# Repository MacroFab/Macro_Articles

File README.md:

***
###Macro_Articles
***
**Files for MacroFab, INC. engineering blog articles.**

This repository contains files and information for articles written on the MacroFab, INC. engineering blog. 

More information can be found on the [MacroFab, INC. engineering blog](https://macrofab.com/blog/engineering). 

***
**License Information**

This project is under the [Creative Commons Attribution-ShareAlike 4.0 International License](LICENSE.md). These files are provided with no warranty and should be used at your own risk. 

***
**Directory listing of the repository**

| Directory | Description |
|---|---|
| AlteraUSBBlaster2TC | Connects the Altera USB Blaster to a TC2050 Tag-Connect Cable. |
| AVR_Tag-Connect | AVR ATmega328P-AU example board using Tag-Connect for programming. |
| AVRISP2TC | Connects AVR ISP programmers to a TC2030 Tag-Connect Cable. | 
| EFM8_Tag-Connect | Tiny example board using Tag-Connect for the EGM8 MCU series. |
| Macro_Duino | MacroFab's version of the ever popular Arduino. Useful for electronic prototyping. |
| MEP_EP_122 | Particle.io Podcast Episode. This is the software written for that episode. |
| MEP_SAO_DC26 | Shitty AddOn for DefCon 26 |
| PCM5122_DAC | DAC PCB board and Test Fixture Files. |
| Resistor_Resistor | 40000 Resistor Array. Designed for the MEP prodcast. |
| SiLabs2TC | Connects the Silicon Labs USB Debug Adapter to a TC2030 Tag-Connect Cable. |
| Simple Programming Fixture | How to design a [simple pogo pin programming fixture](https://macrofab.com/blog/design-build-simple-programming-fixture/). |
| SWD2TC | Connects STLink V2 to a TC2030 Tag-Connect Cable. |
| USB_Type-C_Test | A Parallax Propeller based board that connects over a USB Type-C connector. |

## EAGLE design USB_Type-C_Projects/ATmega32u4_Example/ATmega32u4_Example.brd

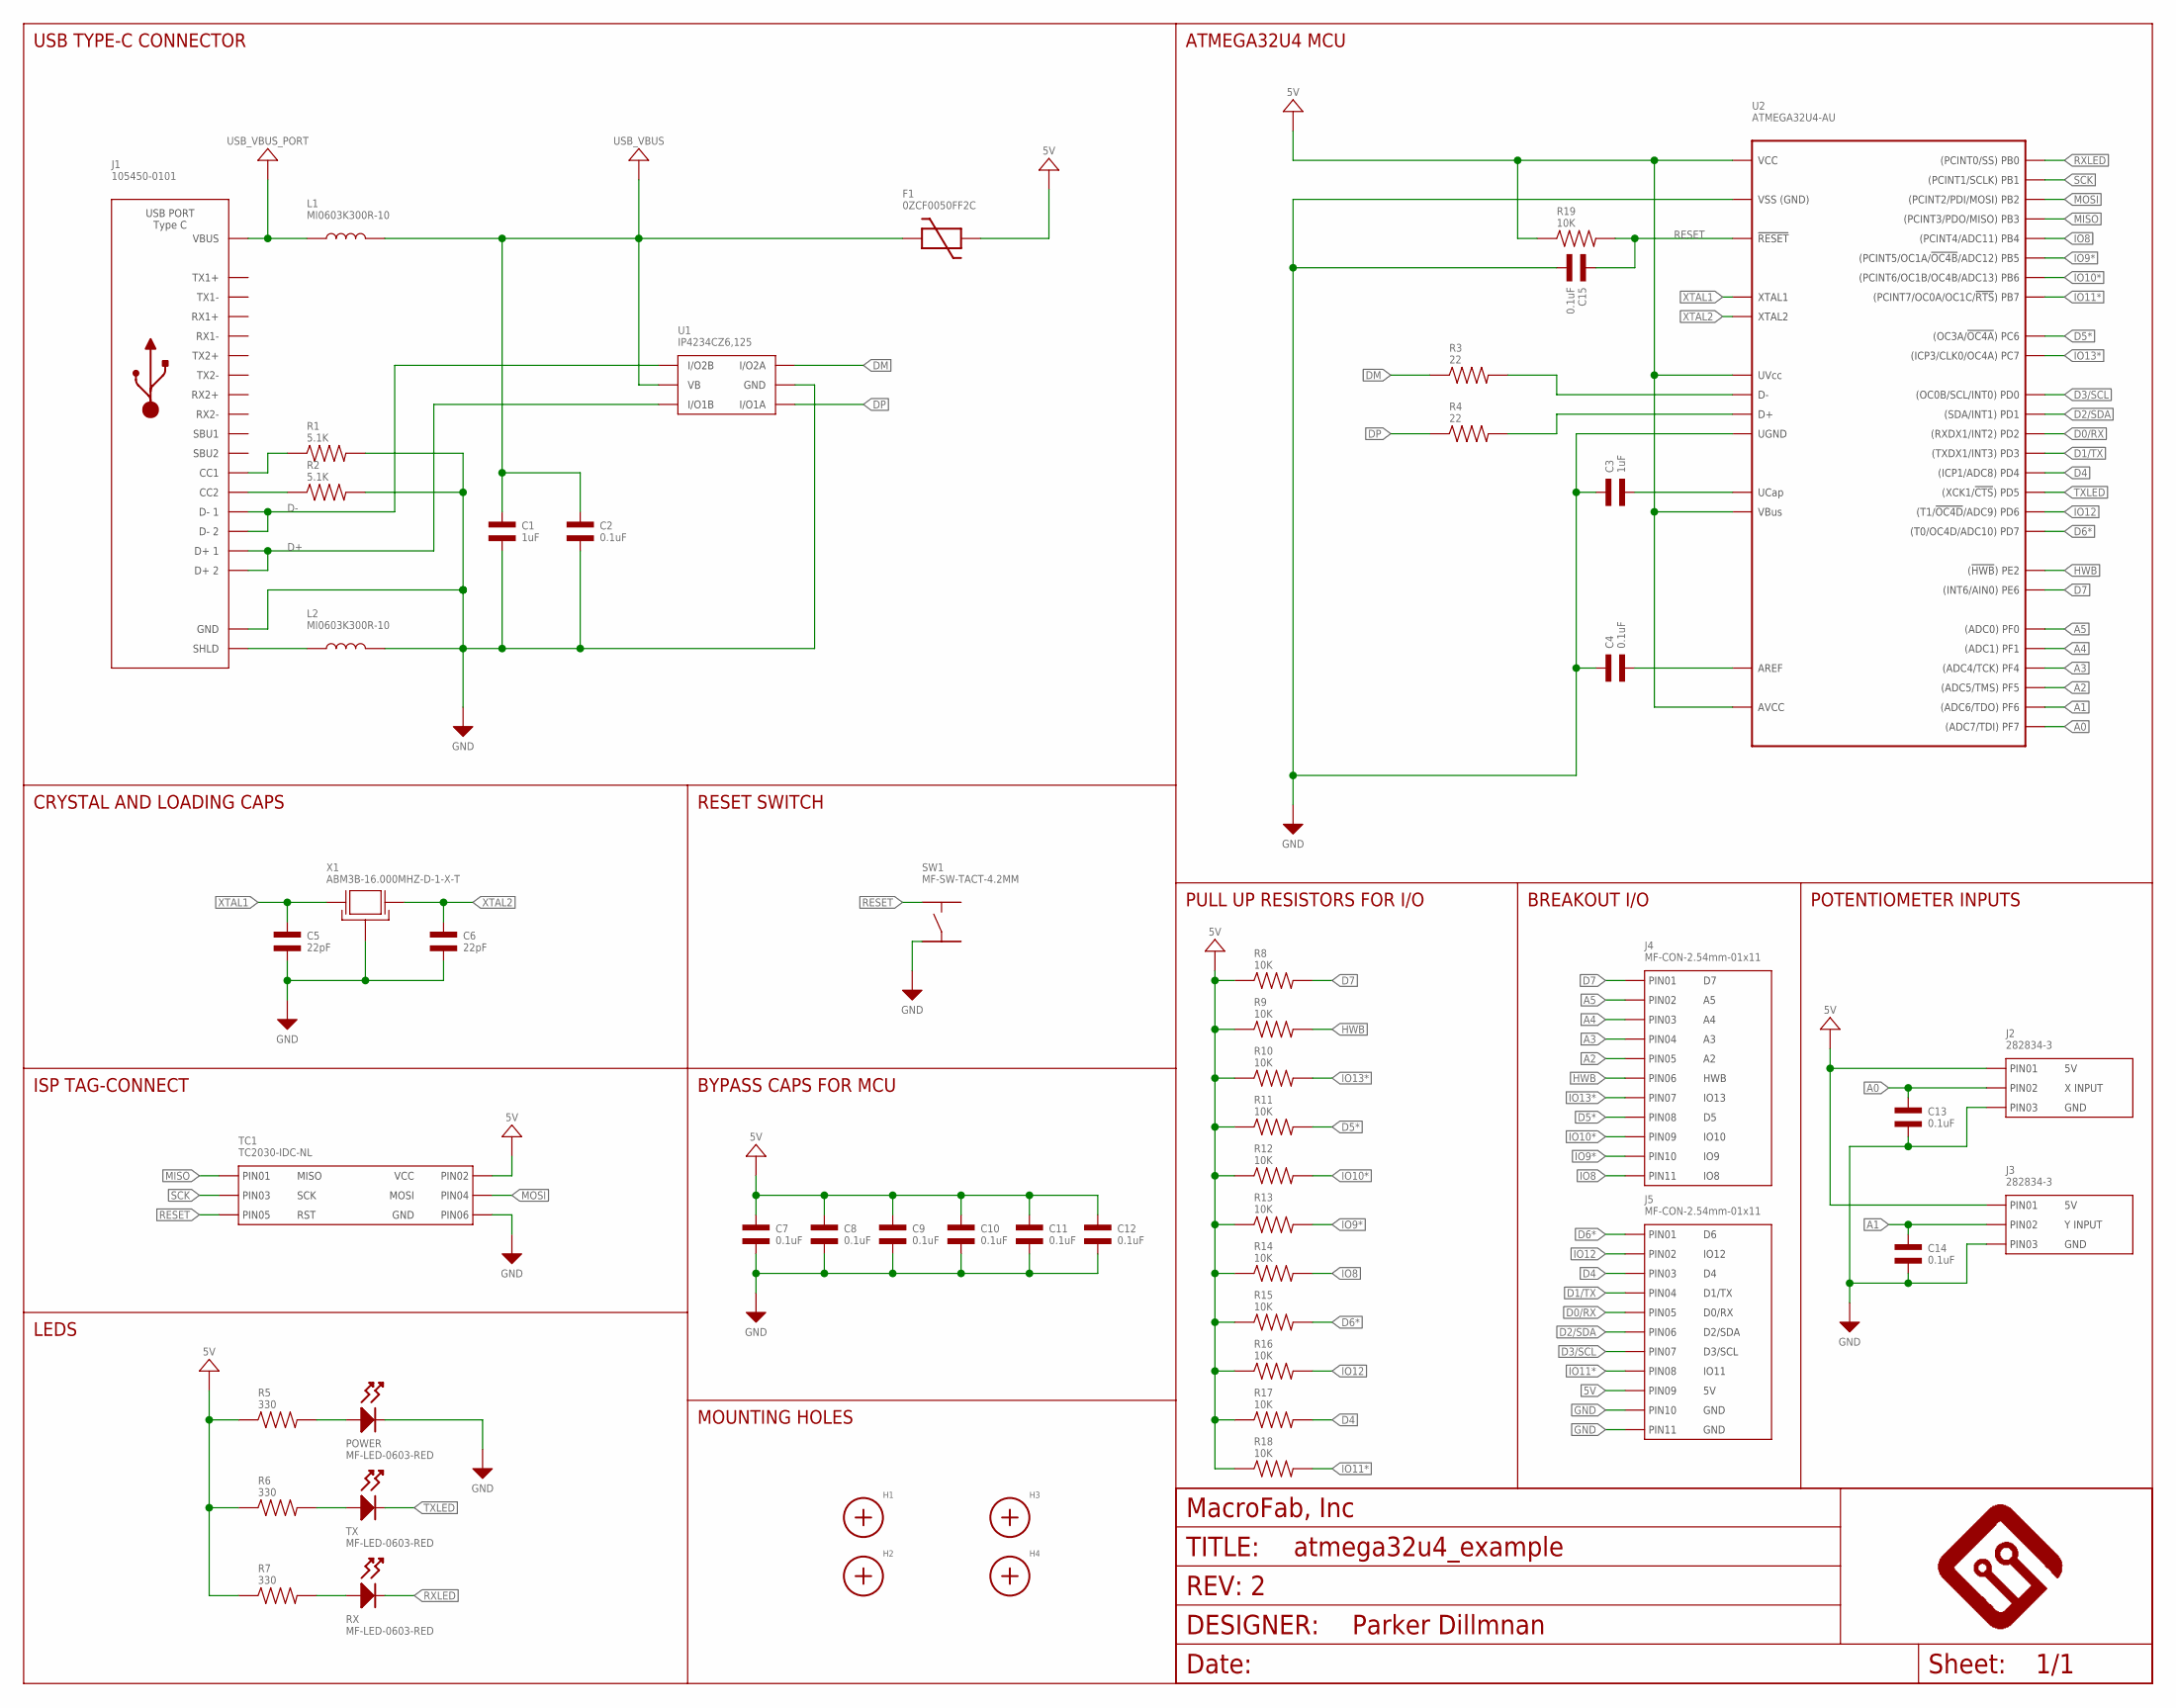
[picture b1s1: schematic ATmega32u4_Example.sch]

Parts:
C1, C3: 1uF; C0603; MPN MF-CAP-0603-1uF
C2, C4, C7, C8, C9, C10, C11, C12, C13, C14, C15: 0.1uF; C0603; MPN MF-CAP-0603-0.1uF
C5, C6: 22pF; C0603; MPN MF-CAP-0603-22pF
F1: 0ZCF0050FF2C; 2920; MPN 0ZCF0050FF2C
FRAME1: MF_FRAMEDEFAULT; MF_FRAME_DEFAULT
H1, H2, H3, H4: MOUNT_HOLE150MIL; MOUNT_HOLE_150MIL
J1: 105450-0101; MPN 105450-0101
J2, J3: 282834-3
J4, J5: MF-CON-2.54mm-01x11; PTH_2.54MM_01X11
L1, L2: MI0603K300R-10; L0603; MPN MI0603K300R-10
POWER: MF-LED-0603-RED; LED0603
R1, R2: 5.1K; R0603; MPN ERJ-3EKF5101V
R3, R4: 22; R0603; MPN MF-RES-0603-22
R5, R6, R7: 330; R0603; MPN MF-RES-0603-330
R8, R9, R10, R11, R12, R13, R14, R15, R16, R17, R18, R19: 10K; R0603; MPN MF-RES-0603-10K
RX: MF-LED-0603-RED; LED0603
SW1: MF-SW-TACT-4.2MM; TACT4.2MM
TC1: TC2030-IDC-NL
TX: MF-LED-0603-RED; LED0603
U1: IP4234CZ6,125; IP4234CZ6_SOT-457-6; MPN IP4234CZ6,125
U2: ATMEGA32U4-AU; TQFP44
X1: ABM3B-16.000MHZ-D-1-X-T; 5MMX3.2MM; MPN ABM3B-16.000MHZ-D-1-X-T

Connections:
5V: C7.P$1, C8.P$1, C9.P$1, C10.P$1, C11.P$1, C12.P$1, F1.2, J2.P$1 (PIN1), J3.P$1 (PIN1), J5.P$9 (PIN9), R5.P$1, R6.P$1, R7.P$1, R8.P$1, R9.P$1, R10.P$1, R11.P$1, R12.P$1, R13.P$1, R14.P$1, R15.P$1, R16.P$1, R17.P$1, R18.P$1, R19.P$1, TC1.P$2 (PIN2), U2.P$2 (UVCC), U2.P$7 (VBUS), U2.P$14 (VCC), U2.P$24 (AVCC), U2.P$34 (VCC), U2.P$44 (AVCC)
A0: C13.P$1, J2.P$2 (PIN2), U2.P$36 (PF7)
A1: C14.P$1, J3.P$2 (PIN2), U2.P$37 (PF6)
A2: J4.P$5 (PIN5), U2.P$38 (PF5)
A3: J4.P$4 (PIN4), U2.P$39 (PF4)
A4: J4.P$3 (PIN3), U2.P$40 (PF1)
A5: J4.P$2 (PIN2), U2.P$41 (PF0)
CC1: J1.A5 (CC1), R1.P$1
CC2: J1.B5 (CC2), R2.P$1
D0/RX: J5.P$5 (PIN5), U2.P$20 (PD2)
D1/TX: J5.P$4 (PIN4), U2.P$21 (PD3)
D2/SDA: J5.P$6 (PIN6), U2.P$19 (PD1)
D3/SCL: J5.P$7 (PIN7), U2.P$18 (PD0)
D4: J5.P$3 (PIN3), R17.P$2, U2.P$25 (PD4)
D5*: J4.P$8 (PIN8), R11.P$2, U2.P$31 (PC6)
D6*: J5.P$1 (PIN1), R15.P$2, U2.P$27 (PD7)
D7: J4.P$1 (PIN1), R8.P$2, U2.P$1 (PE6)
D+: J1.A6 (D+1), J1.B6 (D+2), U1.3 (I/O1B)
D-: J1.A7 (D-1), J1.B7 (D-2), U1.4 (I/O2B)
DM: R3.P$1, U1.6 (I/O2A)
DP: R4.P$1, U1.1 (I/O1A)
GND: C1.P$2, C2.P$2, C3.P$1, C4.P$1, C5.P$2, C6.P$2, C7.P$2, C8.P$2, C9.P$2, C10.P$2, C11.P$2, C12.P$2, C13.P$2, C14.P$2, C15.P$2, J1.A1 (GND), J1.A12 (GND), J1.B1 (GND), J1.B12 (GND), J2.P$3 (PIN3), J3.P$3 (PIN3), J5.P$10 (PIN10), J5.P$11 (PIN11), L2.P$2, POWER.CATHODE, R1.P$2, R2.P$2, SW1.P$3, TC1.P$6 (PIN6), U1.2 (GND), U2.P$5 (UGND), U2.P$15 (GND), U2.P$23 (GND), U2.P$35 (GND), U2.P$43 (GND), X1.P$2 (GND), X1.P$4 (GND)
HWB: J4.P$6 (PIN6), R9.P$2, U2.P$33 (PE2)
IO8: J4.P$11 (PIN11), R14.P$2, U2.P$28 (PB4)
IO9*: J4.P$10 (PIN10), R13.P$2, U2.P$29 (PB5)
IO10*: J4.P$9 (PIN9), R12.P$2, U2.P$30 (PB6)
IO11*: J5.P$8 (PIN8), R18.P$2, U2.P$12 (PB7)
IO12: J5.P$2 (PIN2), R16.P$2, U2.P$26 (PD6)
IO13*: J4.P$7 (PIN7), R10.P$2, U2.P$32 (PC7)
MISO: TC1.P$1 (PIN1), U2.P$11 (PB3)
MOSI: TC1.P$4 (PIN4), U2.P$10 (PB2)
unnamed: R3.P$2, U2.P$3 (D-)
unnamed: R4.P$2, U2.P$4 (D+)
unnamed: C3.P$2, U2.P$6 (UCAP)
unnamed: C4.P$2, U2.P$42 (AREF)
unnamed: POWER.ANODE, R5.P$2
unnamed: R6.P$2, TX.ANODE
unnamed: R7.P$2, RX.ANODE
RESET: C15.P$1, R19.P$2, SW1.P$1, TC1.P$5 (PIN5), U2.P$13 (!RESET)
RXLED: RX.CATHODE, U2.P$8 (PB0)
SCK: TC1.P$3 (PIN3), U2.P$9 (PB1)
SHEILD1: J1.S_T1 (SHLD), J1.S_T2 (SHLD), J1.S_T3 (SHLD), J1.S_T4 (SHLD), L2.P$1
TXLED: TX.CATHODE, U2.P$22 (PD5)
USB_VBUS: C1.P$1, C2.P$1, F1.1, L1.P$2, U1.5 (VB)
USB_VBUS_PORT: J1.A4 (VBUS), J1.A9 (VBUS), J1.B4 (VBUS), J1.B9 (VBUS), L1.P$1
XTAL1: C5.P$1, U2.P$17 (XTAL1), X1.P$1 (X0)
XTAL2: C6.P$1, U2.P$16 (XTAL2), X1.P$3 (X1)

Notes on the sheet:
LEDS
ISP TAG-CONNECT
CRYSTAL AND LOADING CAPS
RESET SWITCH
USB TYPE-C CONNECTOR
BYPASS CAPS FOR MCU
MOUNTING HOLES
ATMEGA32U4 MCU
PULL UP RESISTORS FOR I/O
BREAKOUT I/O
POTENTIOMETER INPUTS

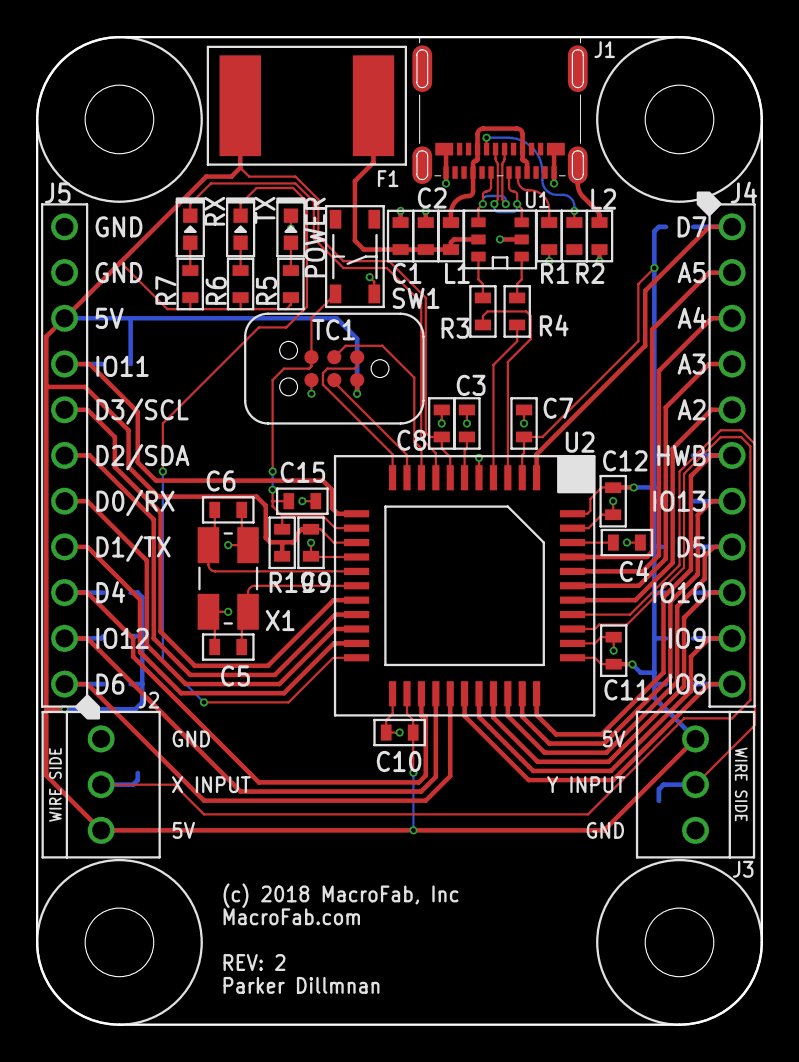
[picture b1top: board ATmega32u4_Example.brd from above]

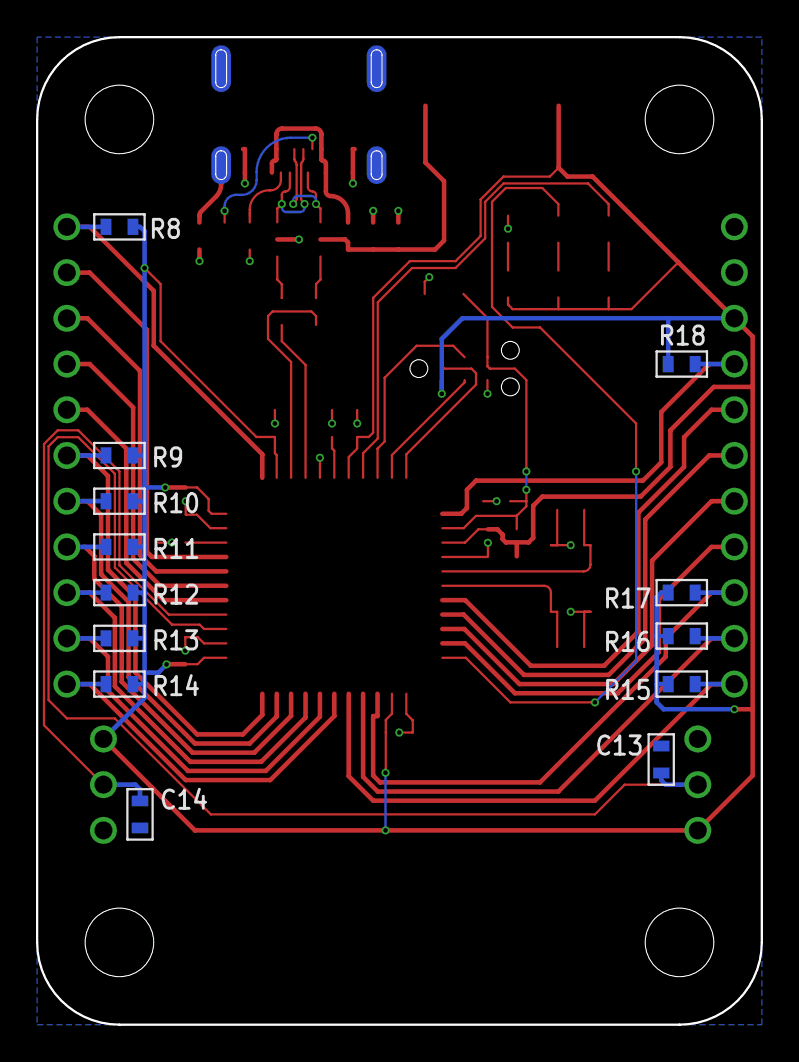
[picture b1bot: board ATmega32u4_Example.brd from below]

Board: 2 copper layers, 40.3 x 54.9 mm, 55 parts (13 on the bottom side), 47 nets.

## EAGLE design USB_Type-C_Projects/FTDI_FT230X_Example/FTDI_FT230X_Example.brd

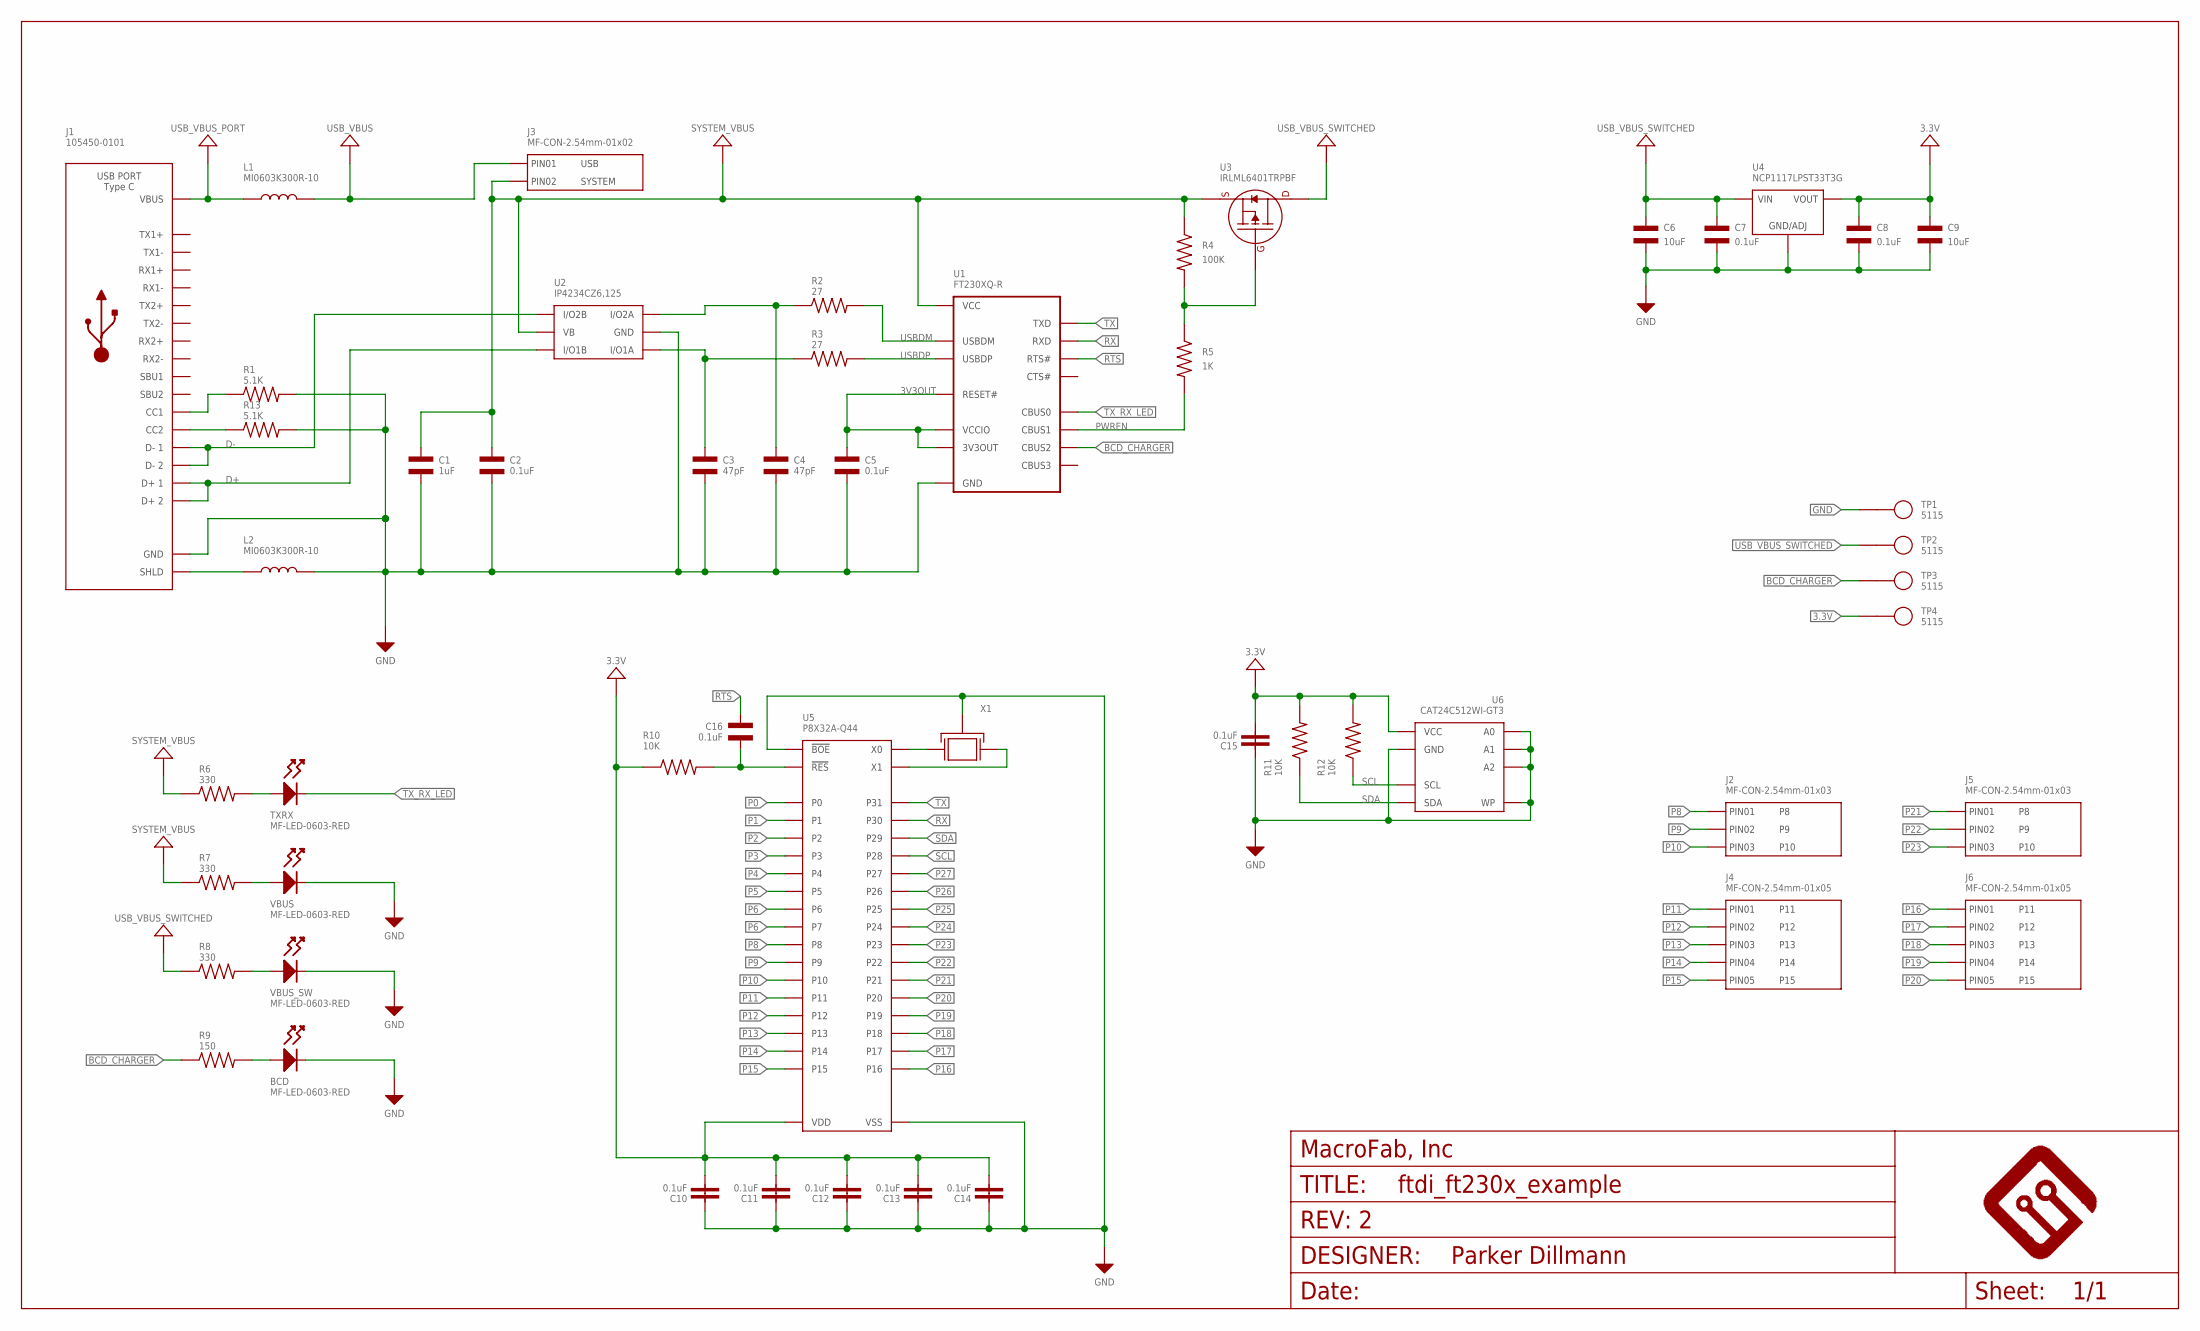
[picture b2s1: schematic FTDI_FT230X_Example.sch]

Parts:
BCD: MF-LED-0603-RED; LED0603
C1: 1uF; C0603; MPN MF-CAP-0603-1uF
C2, C5, C7, C8, C16: 0.1uF; C0603; MPN MF-CAP-0603-0.1uF
C3, C4: 47pF; C0603; MPN C0603C470J1GACTU
C6, C9: 10uF; C1206; MPN MF-CAP-1206-10uF
C10, C11, C12, C13, C14, C15: 0.1uF; 0603; MPN MF-CAP-0603-0.1uF
FRAME1: MF_FRAMEDEFAULT; MF_FRAME_DEFAULT
J1: 105450-0101; MPN 105450-0101
J2, J5: MF-CON-2.54mm-01x03; PTH_2.54MM_01X03
J3: MF-CON-2.54mm-01x02; PTH_2.54MM_01X02
J4, J6: MF-CON-2.54mm-01x05; PTH_2.54MM_01X05
L1, L2: MI0603K300R-10; L0603; MPN MI0603K300R-10
R1, R13: 5.1K; R0603; MPN ERJ-3EKF5101V
R2, R3: 27; R0603; MPN MF-RES-0603-27
R4: 100K; R0603; MPN MF-RES-0603-100K
R5: 1K; R0603; MPN MF-RES-0603-1K
R6, R7, R8: 330; R0603; MPN MF-RES-0603-330
R9: 150; R0603; MPN ERJ-3EKF1500V
R10, R11, R12: 10K; 0603; MPN MF-RES-0603-10K
TP1, TP2, TP3, TP4: 5115; KEYSTONE_5115-5119; MPN Keystone 5115
TXRX: MF-LED-0603-RED; LED0603
U1: FT230XQ-R; FT230X_QFN-16; MPN FT230XQ-R
U2: IP4234CZ6,125; IP4234CZ6_SOT-457-6; MPN IP4234CZ6,125
U3: IRLML6401TRPBF; SOT-23-3; MPN IRLML6401TRPBF
U4: NCP1117LPST33T3G; SOT-223-3
U5: P8X32A-Q44; P8X32A_LQFP-44; MPN P8X32A-Q44
U6: CAT24C512WI-GT3; SOIC-8_W; MPN CAT24C512WI-GT3
VBUS: MF-LED-0603-RED; LED0603
VBUS_SW: MF-LED-0603-RED; LED0603
X1: ABMM-6.000MHZ-B2-T; 7MMX5MM; MPN ABMM-6.000MHZ-B2-T

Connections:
3.3V: C8.P$1, C9.P$1, C10.2, C11.2, C12.2, C13.2, C14.2, C15.2, R10.1, R11.2, R12.2, TP4.P$1, U4.P$1 (VOUT), U4.P$3 (VOUT), U5.8 (VDD), U5.18 (VDD), U5.30 (VDD), U5.40 (VDD), U6.8 (VCC)
3V3OUT: C5.P$1, U1.1 (VCCIO), U1.8 (3V3OUT), U1.9 (RESET#)
BCD_CHARGER: R9.P$1, TP3.P$1, U1.5 (CBUS2)
CC1: J1.A5 (CC1), R1.P$1
CC2: J1.B5 (CC2), R13.P$1
D+: J1.A6 (D+1), J1.B6 (D+2), U2.3 (I/O1B)
D-: J1.A7 (D-1), J1.B7 (D-2), U2.4 (I/O2B)
GND: BCD.CATHODE, C1.P$2, C2.P$2, C3.P$2, C4.P$2, C5.P$2, C6.P$2, C7.P$2, C8.P$2, C9.P$2, C10.1, C11.1, C12.1, C13.1, C14.1, C15.1, J1.A1 (GND), J1.A12 (GND), J1.B1 (GND), J1.B12 (GND), L2.P$2, R1.P$2, R13.P$2, TP1.P$1, U1.3 (GND), U1.13 (GND), U1.PAD (GND), U2.2 (GND), U4.P$2 (GND/ADJ), U5.5 (VSS), U5.6 (!BOE), U5.17 (VSS), U5.27 (VSS), U5.39 (VSS), U6.1 (A0), U6.2 (A1), U6.3 (A2), U6.4 (GND), U6.7 (WP), VBUS.CATHODE, VBUS_SW.CATHODE, X1.P$2 (GND), X1.P$4 (GND)
unnamed: R4.P$2, R5.P$1, U3.1 (GATE)
unnamed: J1.S_T1 (SHLD), J1.S_T2 (SHLD), J1.S_T3 (SHLD), J1.S_T4 (SHLD), L2.P$1
unnamed: R6.P$2, TXRX.ANODE
unnamed: R7.P$2, VBUS.ANODE
unnamed: R8.P$2, VBUS_SW.ANODE
unnamed: BCD.ANODE, R9.P$2
unnamed: C3.P$1, R3.P$1, U2.1 (I/O1A)
unnamed: C4.P$1, R2.P$1, U2.6 (I/O2A)
P0: U5.41 (P0)
P1: U5.42 (P1)
P2: U5.43 (P2)
P3: U5.44 (P3)
P4: U5.1 (P4)
P5: U5.2 (P5)
P6: U5.3 (P6)
P7: U5.4 (P7)
P8: J2.P$1 (PIN1), U5.9 (P8)
P9: J2.P$2 (PIN2), U5.10 (P9)
P10: J2.P$3 (PIN3), U5.11 (P10)
P11: J4.P$1 (PIN1), U5.12 (P11)
P12: J4.P$2 (PIN2), U5.13 (P12)
P13: J4.P$3 (PIN3), U5.14 (P13)
P14: J4.P$4 (PIN4), U5.15 (P14)
P15: J4.P$5 (PIN5), U5.16 (P15)
P16: J6.P$1 (PIN1), U5.19 (P16)
P17: J6.P$2 (PIN2), U5.20 (P17)
P18: J6.P$3 (PIN3), U5.21 (P18)
P19: J6.P$4 (PIN4), U5.22 (P19)
P20: J6.P$5 (PIN5), U5.23 (P20)
P21: J5.P$1 (PIN1), U5.24 (P21)
P22: J5.P$2 (PIN2), U5.25 (P22)
P23: J5.P$3 (PIN3), U5.26 (P23)
P24: U5.31 (P24)
P25: U5.32 (P25)
P26: U5.33 (P26)
P27: U5.34 (P27)
PWREN: R5.P$2, U1.11 (CBUS1)
RES: C16.P$2, R10.2, U5.7 (!RES)
RTS: C16.P$1, U1.16 (RTS#)
RX: U1.2 (RXD), U5.37 (P30)
SCL: R12.1, U5.35 (P28), U6.6 (SCL)
SDA: R11.1, U5.36 (P29), U6.5 (SDA)
SYSTEM_VBUS: C1.P$1, C2.P$1, J3.P$2 (PIN2), R4.P$1, R6.P$1, R7.P$1, U1.10 (VCC), U2.5 (VB), U3.2 (SOURCE)
TX: U1.15 (TXD), U5.38 (P31)
TX_RX_LED: TXRX.CATHODE, U1.12 (CBUS0)
USBDM: R2.P$2, U1.7 (USBDM)
USBDP: R3.P$2, U1.6 (USBDP)
USB_VBUS: J3.P$1 (PIN1), L1.P$2
USB_VBUS_PORT: J1.A4 (VBUS), J1.A9 (VBUS), J1.B4 (VBUS), J1.B9 (VBUS), L1.P$1
USB_VBUS_SWITCHED: C6.P$1, C7.P$1, R8.P$1, TP2.P$1, U3.3 (DRAIN), U4.P$4 (VIN)
X0: U5.29 (X0), X1.P$3 (X1)
X1: U5.28 (X1), X1.P$1 (X0)

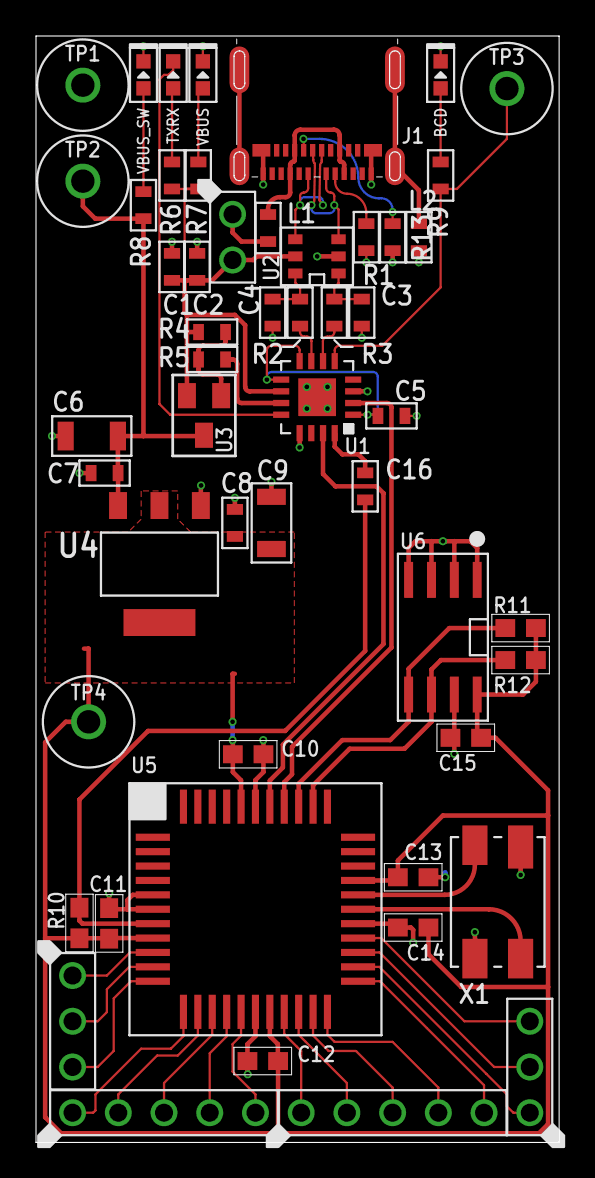
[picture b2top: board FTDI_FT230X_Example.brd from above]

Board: 2 copper layers, 29.0 x 61.4 mm, 53 parts (1 on the bottom side), 48 nets.

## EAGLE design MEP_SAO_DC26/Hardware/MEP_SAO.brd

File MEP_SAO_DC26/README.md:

***
###Macro_Articles
***
**Files for MacroFab, INC. engineering blog articles.**

This repository contains files and information for articles written on the MacroFab, INC. engineering blog. 

More information can be found on the [MacroFab, INC. engineering blog](https://macrofab.com/blog/engineering). 

***
**License Information**

This project is under the [Creative Commons Attribution-ShareAlike 4.0 International License](LICENSE.md). These files are provided with no warranty and should be used at your own risk.

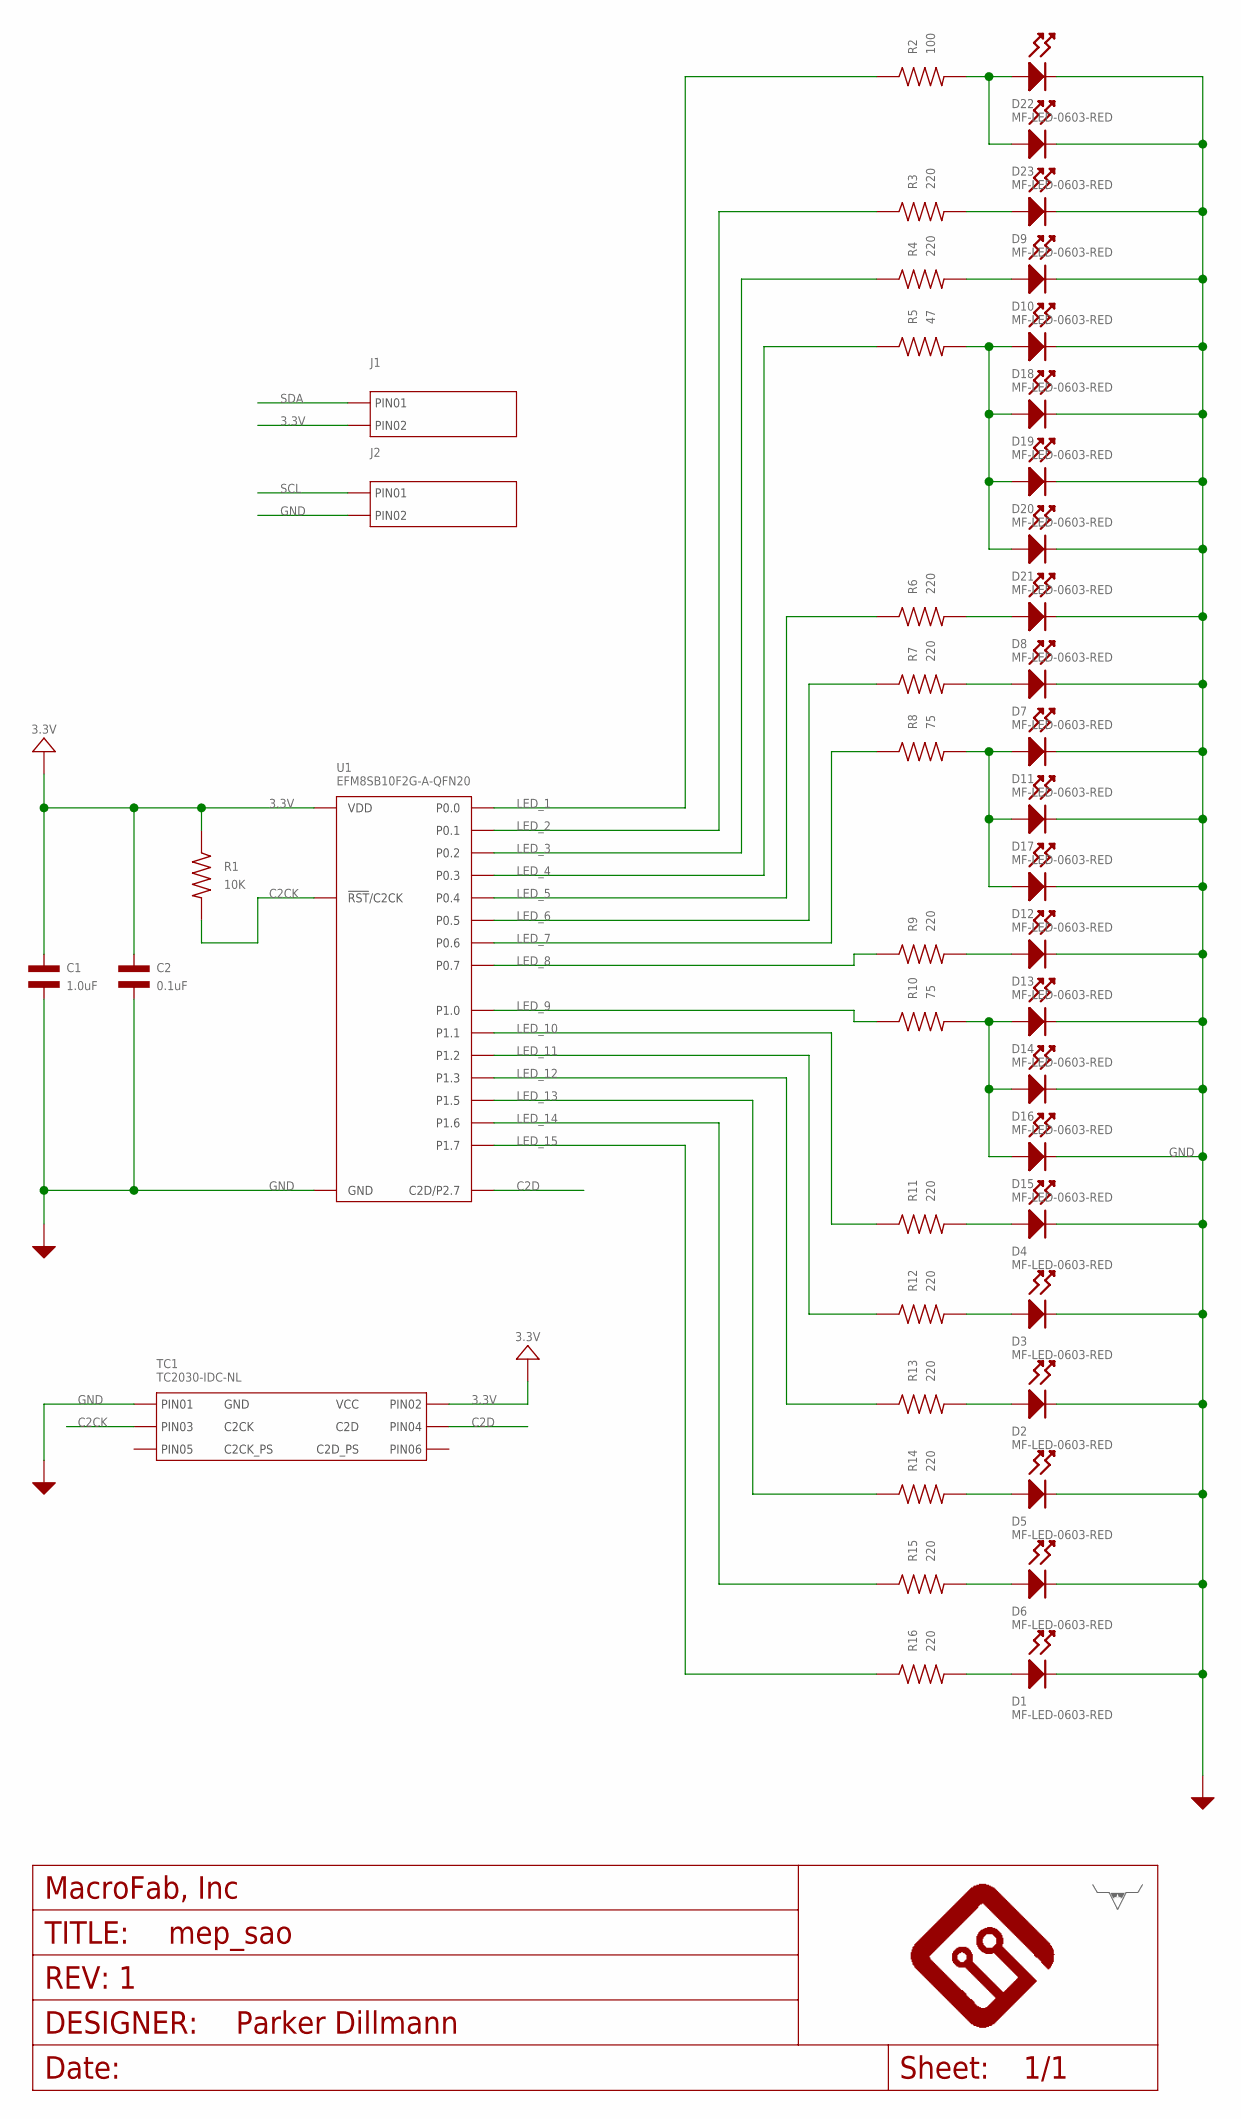
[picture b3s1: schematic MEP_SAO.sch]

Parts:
C1: 1.0uF; C0603; MPN MF-CAP-0603-1uF
C2: 0.1uF; C0603; MPN MF-CAP-0603-0.1uF
D1, D2, D3, D4, D5, D6, D7, D8, D9, D10, D11, D12, D13, D14, D15, D16, D17, D18, D19, D20, D21, D22, D23: MF-LED-0603-RED; LED0603
FRAME1: MF_FRAMEDEFAULT; MF_FRAME_DEFAULT
J1, J2: CON_01X02_2.54MM_PIN_HEADER; 2.54MM_01X02_PIN_HEADER
R1: 10K; R0402; MPN MF-RES-0402-10K
R2: 100; R0402; MPN MF-RES-0402-100
R3, R4, R6, R7, R9, R11, R12, R13, R14, R15, R16: 220; R0402; MPN MF-RES-0402-220
R5: 47; R0402; MPN MF-RES-0402-47
R8, R10: 75; R0402; MPN MF-RES-0402-75
TC1: TC2030-IDC-NL
U1: EFM8SB10F2G-A-QFN20; EFM8SB10F(2/4/8)G-A-QFN20
U$6: LHE_LOGOLHE_LOGO; LHE_LOGO

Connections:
3.3V: C1.P$1, C2.P$1, J1.2 (PIN2), R1.P$1, TC1.P$2 (PIN2), U1.P$4 (VDD)
C2CK: R1.P$2, TC1.P$3 (PIN3), U1.P$5 (!RST!/C2CK)
C2D: TC1.P$4 (PIN4), U1.P$6 (C2D/P2.7)
GND: C1.P$2, C2.P$2, D1.CATHODE, D2.CATHODE, D3.CATHODE, D4.CATHODE, D5.CATHODE, D6.CATHODE, D7.CATHODE, D8.CATHODE, D9.CATHODE, D10.CATHODE, D11.CATHODE, D12.CATHODE, D13.CATHODE, D14.CATHODE, D15.CATHODE, D16.CATHODE, D17.CATHODE, D18.CATHODE, D19.CATHODE, D20.CATHODE, D21.CATHODE, D22.CATHODE, D23.CATHODE, J2.2 (PIN2), TC1.P$1 (PIN1), U1.P$3 (GND), U1.P$12 (GND), U1.PAD (GND)
LED_1: R2.P$1, U1.P$2 (P0.0)
LED_2: R3.P$1, U1.P$1 (P0.1)
LED_3: R4.P$1, U1.P$20 (P0.2)
LED_4: R5.P$1, U1.P$19 (P0.3)
LED_5: R6.P$1, U1.P$18 (P0.4)
LED_6: R7.P$1, U1.P$17 (P0.5)
LED_7: R8.P$1, U1.P$16 (P0.6)
LED_8: R9.P$1, U1.P$15 (P0.7)
LED_9: R10.P$1, U1.P$14 (P1.0)
LED_10: R11.P$1, U1.P$13 (P1.1)
LED_11: R12.P$1, U1.P$11 (P1.2)
LED_12: R13.P$1, U1.P$10 (P1.3)
LED_13: R14.P$1, U1.P$9 (P1.5)
LED_14: R15.P$1, U1.P$8 (P1.6)
LED_15: R16.P$1, U1.P$7 (P1.7)
unnamed: D22.ANODE, D23.ANODE, R2.P$2
unnamed: D18.ANODE, D19.ANODE, D20.ANODE, D21.ANODE, R5.P$2
unnamed: D10.ANODE, R4.P$2
unnamed: D7.ANODE, R7.P$2
unnamed: D1.ANODE, R16.P$2
unnamed: D13.ANODE, R9.P$2
unnamed: D9.ANODE, R3.P$2
unnamed: D8.ANODE, R6.P$2
unnamed: D6.ANODE, R15.P$2
unnamed: D5.ANODE, R14.P$2
unnamed: D2.ANODE, R13.P$2
unnamed: D3.ANODE, R12.P$2
unnamed: D4.ANODE, R11.P$2
unnamed: D14.ANODE, D15.ANODE, D16.ANODE, R10.P$2
unnamed: D11.ANODE, D12.ANODE, D17.ANODE, R8.P$2
SCL: J2.1 (PIN1)
SDA: J1.1 (PIN1)

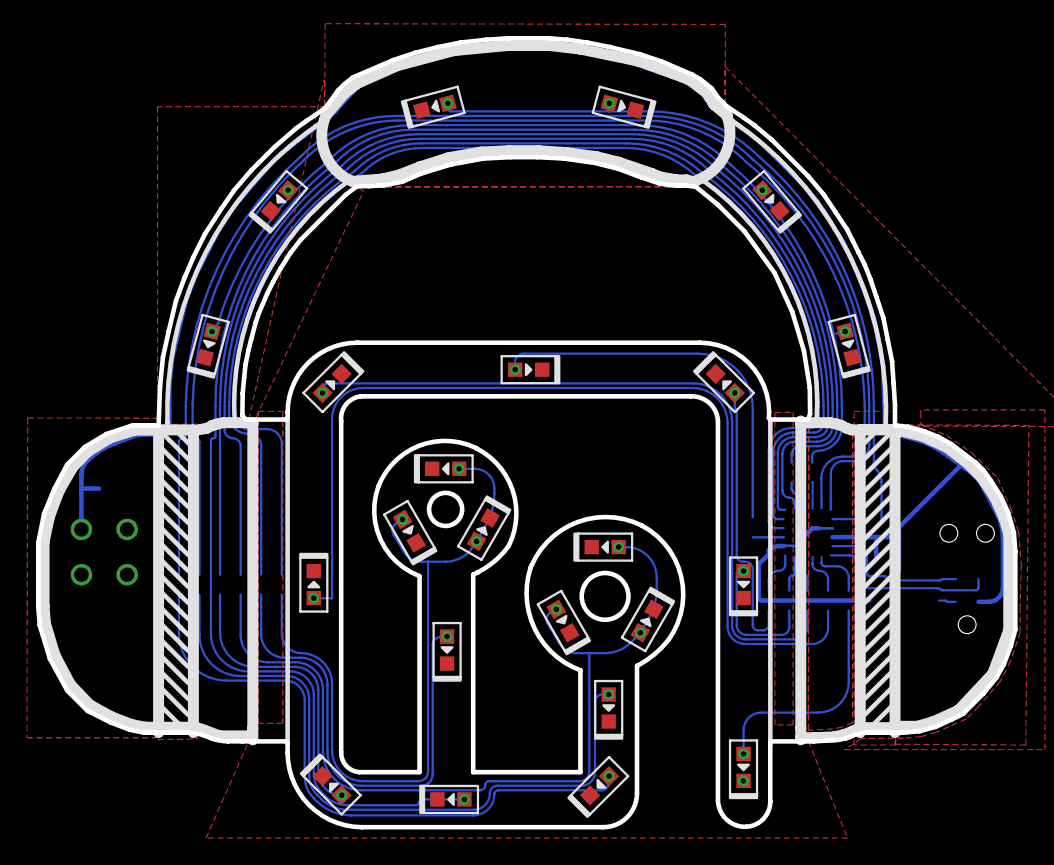
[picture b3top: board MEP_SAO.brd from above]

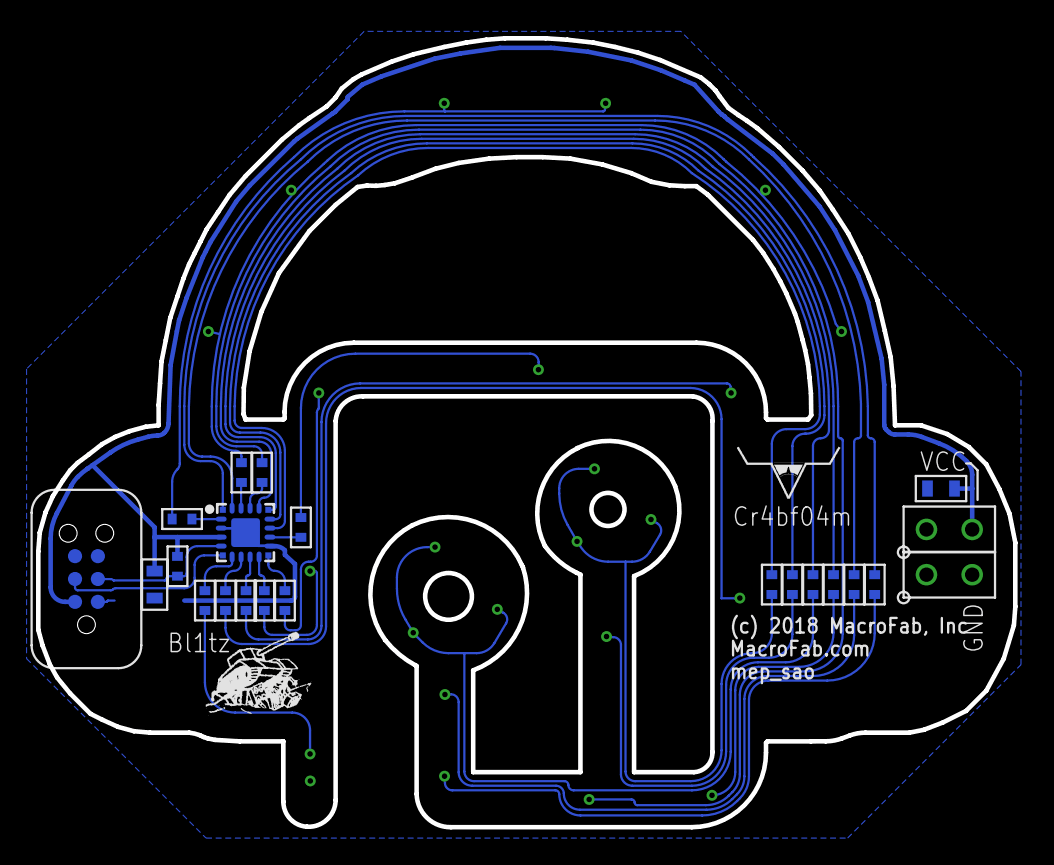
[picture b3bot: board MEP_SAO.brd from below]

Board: 2 copper layers, 54.3 x 43.8 mm, 47 parts (24 on the bottom side), 34 nets.

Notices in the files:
parts and their libraries:
MF_Aesthetics: (c) 2016 MacroFab, Inc
MF_Aesthetics: (c) 2018 MacroFab, Inc
PP_Aesthetics: (c) 2018 Longhorn Engineer
